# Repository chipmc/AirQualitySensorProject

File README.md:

AirQualitySensorProject
=======================

This is an Internet of Things Project to build an Air Quality sensor

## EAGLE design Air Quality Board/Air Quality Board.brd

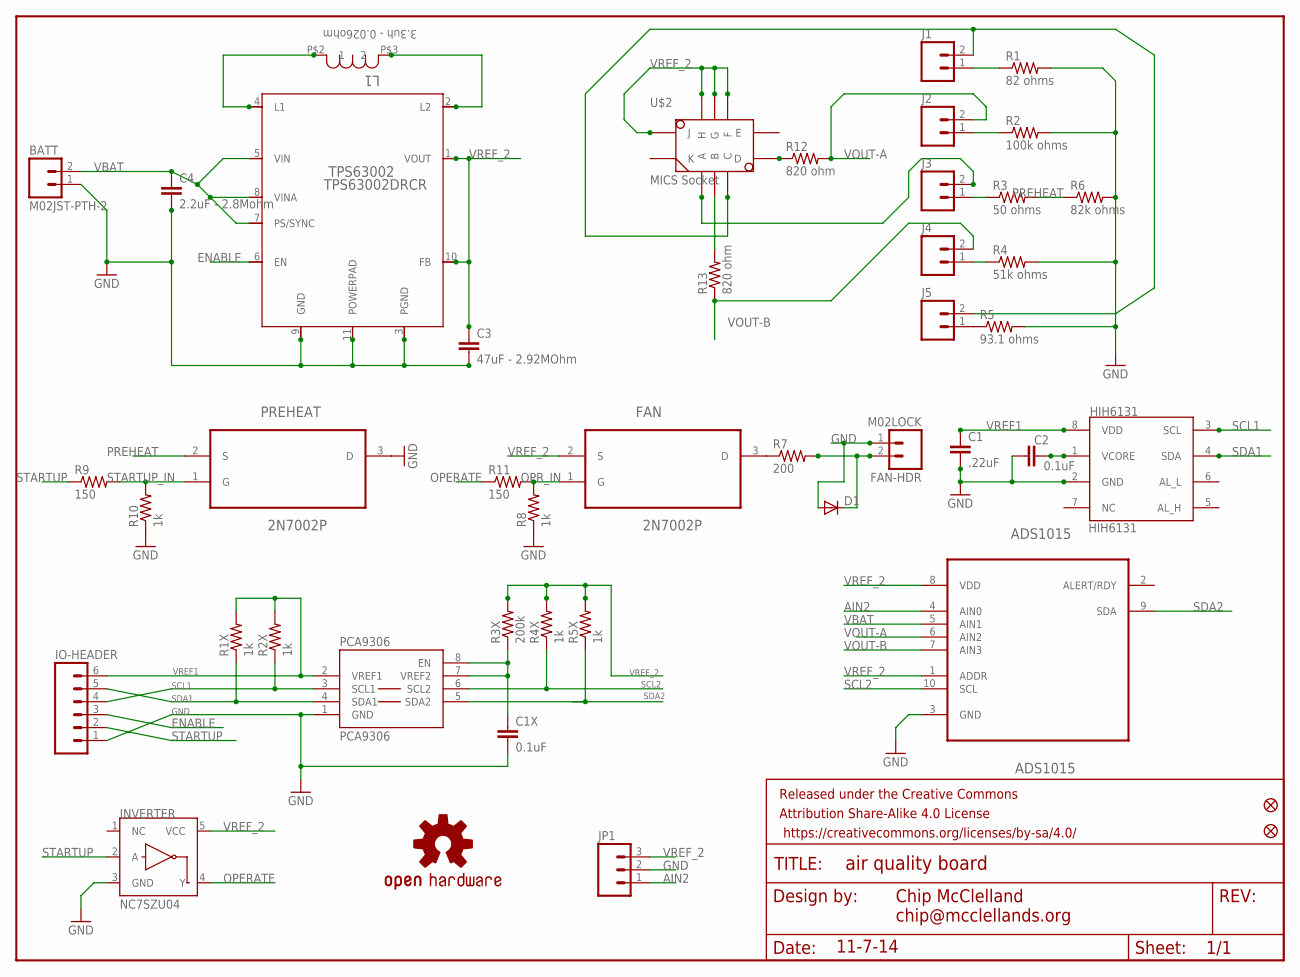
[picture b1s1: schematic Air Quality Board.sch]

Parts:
ADS1015: ADS1015; SOP50P490X110-10N
BATT: M02JST-PTH-2; JST-2-PTH
C1: .22uF; 0805
C1X, C2: 0.1uF; 0805
C3: 47uF - 2.92MOhm; 0805
C4: 2.2uF - 2.8Mohm; 1206
D1: DIODESMA; SMA-DIODE
FAN: 2N7002P; SOT95P230X110-3N
FAN-HDR: M02LOCK; 1X02_LOCK
FRAME1: FRAME-LETTER; CREATIVE_COMMONS
HIH6131: HIH6131; SOIC8
IO-HEADER: M06LOCK; 1X06_LOCK
J1, J2, J3, J4, J5: M02LOCK; 1X02_LOCK
JP1: M03LOCK; 1X03_LOCK
JP7, JP8: FIDUCIAL1X2.5; FIDUCIAL-1X2.5
L1: 3.3uh - 0.026ohm; POWERINDUCTOR
LOGO1: OSHW-LOGOS; OSHW-LOGO-S
NC7SZU04: INVERTER; SOT23-5
PCA9306: PCA9306; SOIC8
PREHEAT: 2N7002P; SOT95P230X110-3N
R1: 82 ohms; 0805
R1X, R2X, R4X, R5X, R8, R10: 1k; 0805
R2: 100k ohms; 0805
R3: 50 ohms; 0805
R3X: 200k; 0805
R4: 51k ohms; 0805
R5: 93.1 ohms; 0805
R6: 82k ohms; 0805
R7: 200; 0805
R9, R11: 150; 0805
R12, R13: 820 ohm; 0805
TPS63002: TPS63002DRCR; NEW-S-PVSON-N10
U$2: MICS Socket; MICS-SMD-SOCKET

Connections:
AIN2: ADS1015.4 (AIN0), JP1.1
ENABLE: IO-HEADER.3, TPS63002.6 (EN)
FAN: FAN.3 (D), R7.1
GND: ADS1015.3 (GND), BATT.1, C1.2, C1X.2, C2.1, C3.2, C4.2, D1.A, FAN-HDR.1, HIH6131.2 (GND), IO-HEADER.1, JP1.2, NC7SZU04.3 (GND), PCA9306.1 (GND), PREHEAT.3 (D), R1.2, R2.2, R4.2, R5.2, R6.2, R8.1, R10.1, TPS63002.3 (PGND), TPS63002.9 (GND), TPS63002.11 (POWERPAD)
J1: J1.2, J5.2, U$2.C
J3: J3.2, U$2.A
unnamed: J5.1, R5.1
unnamed: J4.1, R4.1
unnamed: J3.1, R3.1
unnamed: J2.1, R2.1
unnamed: J1.1, R1.1
unnamed: R13.2, U$2.B
unnamed: L1.P$2 (1), TPS63002.4 (L1)
unnamed: L1.P$3 (2), TPS63002.2 (L2)
unnamed: R12.1, U$2.D
unnamed: D1.C, FAN-HDR.2, R7.2
unnamed: C2.2, HIH6131.1 (VCORE)
OPERATE: NC7SZU04.4 (Y), R11.1
OPR_IN: FAN.1 (G), R8.2, R11.2
PREHEAT: PREHEAT.2 (S), R3.2, R6.1
SCL1: HIH6131.3 (SCL), IO-HEADER.4, PCA9306.3 (SCL1), R2X.1
SCL2: ADS1015.10 (SCL), PCA9306.6 (SCL2), R4X.1
SDA1: HIH6131.4 (SDA), IO-HEADER.5, PCA9306.4 (SDA1), R1X.1
SDA2: ADS1015.9 (SDA), PCA9306.5 (SDA2), R5X.1
STARTUP: IO-HEADER.2, NC7SZU04.2 (A), R9.1
STARTUP_IN: PREHEAT.1 (G), R9.2, R10.2
VBAT: ADS1015.5 (AIN1), BATT.2, C4.1, TPS63002.5 (VIN), TPS63002.7 (PS/SYNC), TPS63002.8 (VINA)
VOUT-A: ADS1015.6 (AIN2), J2.2, R12.2
VOUT-B: ADS1015.7 (AIN3), J4.2, R13.1
VREF1: C1.1, HIH6131.8 (VDD), IO-HEADER.6, PCA9306.2 (VREF1), R1X.2, R2X.2
VREF2: C1X.1, PCA9306.7 (VREF2), PCA9306.8 (EN), R3X.1
VREF_2: ADS1015.1 (ADDR), ADS1015.8 (VDD), C3.1, FAN.2 (S), JP1.3, NC7SZU04.5 (VCC), R3X.2, R4X.2, R5X.2, TPS63002.1 (VOUT), TPS63002.10 (FB), U$2.F, U$2.G, U$2.H, U$2.J

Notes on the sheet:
Chip McClelland chip@mcclellands.org
11-7-14

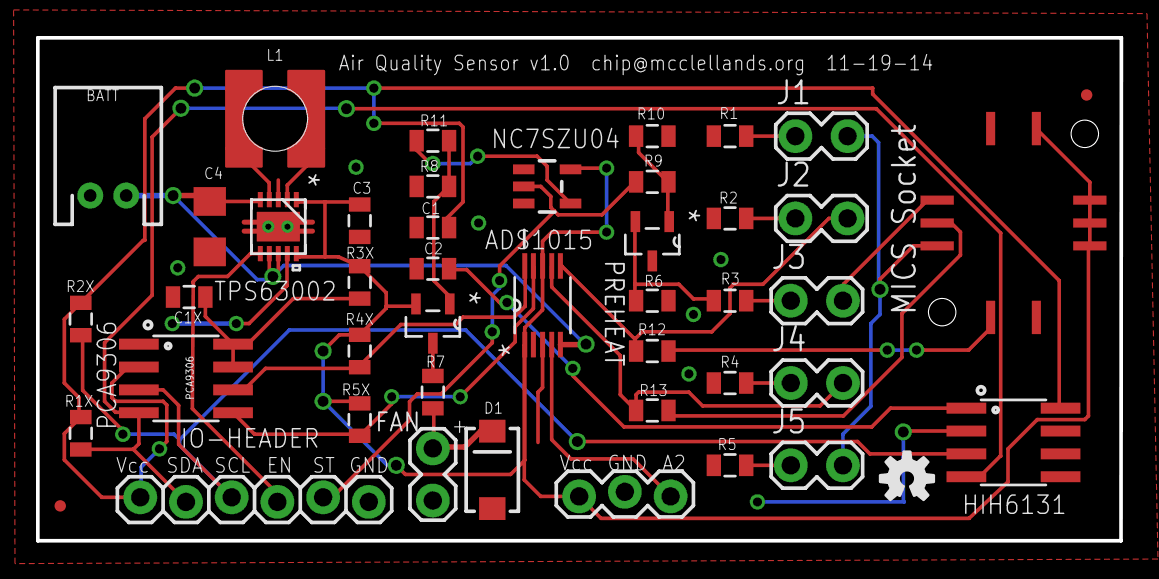
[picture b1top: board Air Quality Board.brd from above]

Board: 2 copper layers, 60.2 x 27.9 mm, 46 parts (0 on the bottom side), 32 nets.

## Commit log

2014-11-21 Added BOM Analysis Spreadsheet
2014-11-21 Added the EAGLE Files
2014-12-04 Added the First Sketch to Connect LinkIt ONE to Ubidots
2014-12-05 Added GPS Data to Ubidots reporting
    Just added GPS using the LinkIt ONE’s built in GPS
2014-12-06 Basic Temp Logger
    Moved Ubidots to a function to make main loop cleaner
2016-05-09 Initial Load

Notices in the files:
parts and their libraries:
SparkFun-DigitalIC: Licensing: CC v3.0 Share-Alike You are welcome to use this library for commercial purposes.
SparkFun-Passives: Licensing: Creative Commons ShareAlike 4.0 International - https://creativecommons.org/licenses/by-sa/4.0
SparkFun-Aesthetics: Released under the Creative Commons
